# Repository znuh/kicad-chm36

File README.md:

# kicad-chm36
Interactive Web Browser based KiCad PCB to CHM-T36VA Pick&amp;Place File Converter  

This tool directly generates a CHM DPV file from a `.kicad_pcb` file (without exporting a `.pos` file in KiCad before).

**Conversion is done entirely in the browser. No PCB or Pick&amp;Place data is sent to a server.**  
Also, the tool only uses locally hosted (i.e. no external CDNs) [Bootstrap5](https://getbootstrap.com/) and vanilla Javascript **without** jQuery, Node.js, etc.

You can try it here: [https://znu.nz/kicad-chm36/](https://znu.nz/kicad-chm36/)

## Current Limitations
* PCB height cannot be set (yet)
* Single PCB mode only (no batch/array mode yet)
* Centroid correction not supported yet
* PCBs should be KiCad Version 8.0 or 7.0 (other versions might or might not work)

## Screenshot

## Basic Installation Instructions
* make the contents of the `web/` directory available via a HTTPS server
* use a browser to access the resource
* Chromium/Chrome instead of Firefox is recommended because Firefox does not (yet) implement the [window.showSaveFilePicker](https://developer.mozilla.org/en-US/docs/Web/API/Window/showSaveFilePicker#browser_compatibility) method. (Firefox will still work, but it'll just download the generated pick&amp;place file instead of showing a Save File Dialog.)

## Using the accompanying Golang Webserver in `server/`
**Note:** This webserver is optional. You can use any HTTPS webserver. This server offers an additional feature (see below) - if you don't need it you can use any HTTPS server. (You can then skip this section.)  
**Note:** While the server per se should work on Windows as well, instructions below are for UNIX-like Operating Systems (e.g. Linux, OSX, \*BSD).

`server/` contains a small HTTPS server written in Golang. Apart from serving the `web/` directory via HTTPS, this server can also serve all KiCad PCBs from a user-specified directory and all subdirectories. This can improve your workflow if the PCB files are located on a different computer than the PnP machine is connected to. You can also reload PCB files after they changed.  
It looks like this on the client side:  
  
To use the server you need to do the following:
* Install a working Golang environment and OpenSSL (for HTTPS cert/key generation)
* run `cd server/ && go build;cd ..`
* there should be a binary called `kicad-server` in the `server/` directory now
* you can now run the `./run_server.sh` script to test the server  
It will generate a key+certificate and start the server offering the test PCB from the `examples/` directory.

After this works you should modify the `./run_server.sh` script to fit your needs:
* Clients must be whitelisted with the `-allowed-ips=` option. You can specify single IPs and/or IP ranges.
* KiCad PCBs from the directory given with `-serve-pcbs=` (including all subdirectories) will be served. Only files with a `.kicad_pcb` suffix will be served.
* No PCBs will be served if the `-serve-pcbs=` option isn't given.

**Note:** The DPV reference file must be located on the client. The server does not offer a DPV reference file to the client.

## Matching PCB Components to Pick&amp;Place Feeders
The CHM DPV (CSV) file format doesn't have dedicated fields for listing the params of the components held by the feeders. There is only a `Note` field which can be used to store component information for a feeder. Instead of using an extra file to hold the component params for the feeders, this tool expects all relevant component params in the `Note` field of the feeder definitions.  
When entering the `Note` for a feeder, the CharmHigh software restricts the number of characters and blocks several characters. This can be overcome by using a text editor to edit the `Note` field. (Any simple editor such as Notepad is fine.) A long `Note` field is usually fine for the CHM software when loading a DPV file - even long Notes are usually displayed just fine. The length limit is only imposed during user input.  
When modifying the `Note` field with an editor you can also use nearly all characters such as spaces, dots and (semi)colons. **You must not use commas and line breaks though** because DPV files are CSV files with a comma separator. You cannot escape commas and quoting text also does not help. So just don't put a comma (or a line break) into the `Note` field.

This tool employs a reasonably intelligent approach for matching KiCad components to Pick&amp;Place feeders. A match occurs when the following conditions are satisfied:
* The KiCad **footprint** identifier (e.g. `C_0402_1005Metric`) must be found somewhere in the **Feeder Note**.
* After this the **KiCad Value** and the **Feeder Note** are treated as lists of whitespace separated params. (i.e. you put at least one space between different params - e.g.: `1uF 10V X5R`)
* The **first value** in this list is called the *Primary Value*. The *Primary Value* from KiCad and a feeder must be equal.  
  * **Units** are optional - e.g. a `10k` KiCad Primary Value will match a `10k` and a `10kR` feeder note.  
(Units are optional because the KiCad footprint identifier already includes the component type C/R/etc.)
  * However, if both the KiCad primary value and the Feeder Note primary value have a unit then these units must match.
  * Units `R` and `Ω` are treated as equivalent. (e.g. `10kR` and `10kΩ` will match)
  * Value comparison honors **multipliers** such as `p/n/u/µ/m/k/M/G` - i.e. `0.1uF` matches `0.1µF` and `100nF`; `10000` and `10k` also match.
  * **Limitation:** `1k5` will **not** match `1.5k`. Just avoid using the multiplier as the decimal point.
* While the KiCad and Feeder Primary Values must be equal for a match, there are also *Secondary Values* such as **ratings and tolerances**. For these values the Feeder Value must be **same or better** than the KiCad Value for a match.
  * Secondary Values are recognized by their unit (ratings: `V/A/W`, tolerances: `%/ppm`). If they are not recognized as rating or tolerance they must match exactly.
  * All KiCad Secondary Values must be satisfied by a Secondary Value from the Feeder Note.  
(Secondary Values only found in the Feeder Note but not in the KiCad Value are ignored - i.e. they don't inhibit a match.)
  * For **ratings** the feeder value must be equal or greater than the KiCad value
  * For **tolerances** the feeder value must be equal or less than the KiCad value
  * **Limitation 1:** Fractional notation (e.g. `1/8W`) isn't supported. Use notation with a decimal point (e.g. `0.125W`) instead.
  * **Limitation 2:** Temperature Coefficients such as **X7R** aren't recognized. This means that they must match exactly. A feeder with *X7R* in the note will not match a KiCad Value containing *X5R*. (If you don't add *X5R* to the KiCad value it can match the feeder if the other values are ok.)

The DPV and KiCad PCB files from the [examples](https://github.com/znuh/kicad-chm36/tree/main/examples) directory are selected to demonstrate several of the matching rules explained here.

### Feeder Note Example: ###
`0.1uF 25V X5R 10% fp:C_0402_1005Metric pn:CL05A104KA5NNNC`  
Note 1: I usually add the exact part number marked with `pn:` at the end of the Feeder Note. This does not break component matching.  
Note 2: I also prefer to prefix the footprint with `fp:` in the Feeder Note. This is also ok because for a match to occur the KiCad footprint identifier (`C_0402_1005Metric`) only needs to be found *somewhere* in the Feeder Note.

## Additional Named Feeder Params
The CHM DPV file format doesn't store the nozzle to use for a feeder in the Feeder Definition but in the individual component placement instruction (`PHead` as in PickHead in the `EComponent` lines). The DPV file also does not store the rotation of components in a certain feeder. Instead there's only the relative rotation of a component to apply during placement of a component. (`Angle` in the `EComponent` lines.)  
**Named Params** in the `Notes` field of a Feeder can be given to specify the **rotation** of components held in this feeder and to choose the **nozzle** to use for the Feeder:
* `nozzle:1` sets the nozzle to 1 (left nozzle). Nozzle 2 is the right nozzle. **Nozzle 1** will be used as the **default** when no **nozzle** param is given. (So you can just omit `nozzle:1` for nozzle 1.)
* `orientation:<angle>` can be used to specify the component rotation in a feeder relative to the KiCad 0° orientation. For reel feeders (Feeder IDs below 60) this is usually +90° (resulting in a -90° rotation to apply for a KiCad component with 0° orientation.)  
Specify the orientation without the degree sign - e.g. `orientation:90` / `orientation:-90`.  
When no component orientation is given for a feeder, a default orientation is selected based on the **Feeder ID**:
  * The default for IDs **below 60** (reel feeders) is a component orientation of +90°
  * The default for ID **60 and above** (IC trays and vibration feeders) is 0°  
* You can omit the `orientation:` param when the default orientation is correct.

## Preparing a DPV Reference File
Any existing DPV file can be used as a reference file - usually only minor modifications to the Feeder Notes are necessary. (See last two sections and the [example reference file](https://github.com/znuh/kicad-chm36/blob/main/examples/reference_example.dpv).)  
You can also create a new DPV file with the CharmHigh software if you do not have a DPV file yet.
Ensure that at least one `EComponent` line can be found in the DPV reference file. (It will be used as a template.)

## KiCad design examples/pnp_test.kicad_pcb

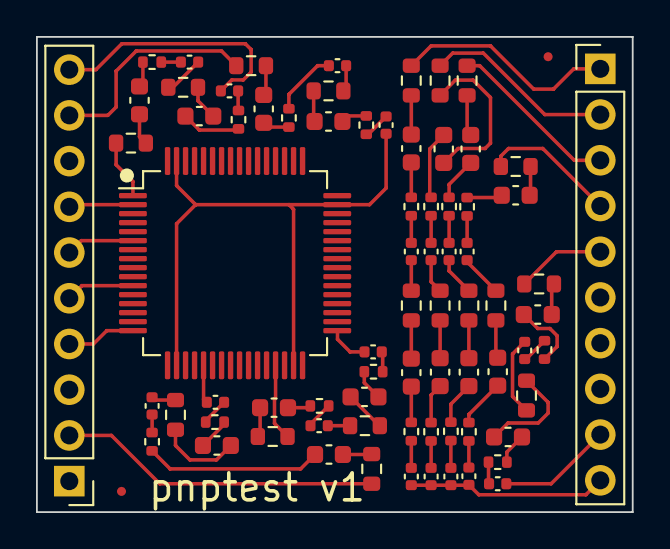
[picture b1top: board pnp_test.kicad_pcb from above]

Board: 2 copper layers, 33.1 x 26.4 mm, 77 parts (0 on the bottom side), 80 nets.

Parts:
C1, C3, C7, C17, C23, C31: 0.1uF; C_0402_1005Metric
C2, C6, C10, C12, C14, C16, C18, C20, C22, C24, C26, C30, C32, C34, C36: 0.1uF; C_0603_1608Metric
C4: 0.1u; C_0603_1608Metric
C5: 100nF; C_0402_1005Metric
C8: 0.1uF X7R 57V; C_0603_1608Metric
C9: 100nF 3V; C_0402_1005Metric
C11: 0.1µF 1V X5R; C_0402_1005Metric
C13: 0.1uF 5V; C_0402_1005Metric
C15: 100nF X5R; C_0402_1005Metric
C19: 0.1uF 11% 5V; C_0402_1005Metric
C21: 0.1uF 3nH; C_0402_1005Metric
C25: 100n; C_0402_1005Metric
C27: 0.1u; C_0402_1005Metric
C28: 0.10001uF; C_0603_1608Metric
C29: 0.1uF 2%; C_0402_1005Metric
C33: 0.1uF 20% 50V; C_0402_1005Metric
C35: 0.1µ; C_0402_1005Metric
FID1, FID2: Fiducial; Fiducial_0.5mm_Mask1.5mm
J1, J2: Conn_01x10_Pin; PinHeader_1x10_P2.54mm_Vertical
R1: 10k 0.0625W 1%; R_0402_1005Metric
R2, R4, R6, R8, R10, R12, R14, R16, R24, R26, R28, R30, R34, R36: 10k; R_0603_1608Metric
R3: 10k 1%; R_0402_1005Metric
R5, R7, R9, R13, R17, R19, R23, R25, R29, R33: 10k; R_0402_1005Metric
R11: 10k 0.06W; R_0402_1005Metric
R15: 10k 2W 1% 50kV; R_0402_1005Metric
R18: 10000R; R_0603_1608Metric
R20: 10kR; R_0603_1608Metric
R21: 10k 5% 10ppm; R_0402_1005Metric
R22: 10000; R_0603_1608Metric
R27: 10000Ω; R_0402_1005Metric
R31: 10k 49V; R_0402_1005Metric
R32: 10.001k; R_0603_1608Metric
R35: 10kΩ 50V; R_0402_1005Metric
U1: STM32F730R8Tx; LQFP-64_10x10mm_P0.5mm

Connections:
/1: R4.2, U1.1 (VBAT)
/2: J1.7, U1.2 (PC13)
/4: J1.4, U1.16 (PA2)
/5: J1.5, U1.11 (PC3)
/6: J1.6, U1.6 (PH1)
/21: C9.1, U1.21 (PA5)
/Ax1: J2.1, R28.2
/Ax2: J2.2, R32.2
/Ax3: J2.3, R36.2
/Ax4: J2.4, R16.2
/Ax5: J2.5, R20.2
/Ax9: C17.1, J2.9
/Ax10: C13.1, C25.1, C29.1, C33.1, J2.10
/Bx9: J1.9, R24.2
/Bx10: C1.1, J1.10
/x2: J1.2, R12.2
GND: C21.1, U1.18 (VSS), U1.31 (VSS), U1.47 (VSS), U1.63 (VSS)
unnamed: C1.2, R1.1
unnamed: C2.1, R1.2
unnamed: C2.2, R2.1
unnamed: C3.1, R2.2
unnamed: C3.2, R3.1
unnamed: C4.1, R3.2
unnamed: C4.2, R4.1
unnamed: C5.2, R5.1
unnamed: C6.1, R5.2
unnamed: C6.2, R6.1
unnamed: C7.1, R6.2
unnamed: C7.2, R7.1
unnamed: C8.1, R7.2
unnamed: C8.2, R8.1
unnamed: C9.2, R9.1
unnamed: C10.1, R9.2
unnamed: C10.2, R10.1
unnamed: C11.1, R10.2
unnamed: C11.2, R11.1
unnamed: C12.1, R11.2
unnamed: C12.2, R12.1
unnamed: C13.2, R13.1
unnamed: C14.1, R13.2
unnamed: C14.2, R14.1
unnamed: C15.1, R14.2
unnamed: C15.2, R15.1
unnamed: C16.1, R15.2
unnamed: C16.2, R16.1
unnamed: C17.2, R17.1
unnamed: C18.1, R17.2
unnamed: C18.2, R18.1
unnamed: C19.1, R18.2
unnamed: C19.2, R19.1
unnamed: C20.1, R19.2
unnamed: C20.2, R20.1
unnamed: C21.2, R21.1
unnamed: C22.1, R21.2
unnamed: C22.2, R22.1
unnamed: C23.1, R22.2
unnamed: C23.2, R23.1
unnamed: C24.1, R23.2
unnamed: C24.2, R24.1
unnamed: C25.2, R25.1
unnamed: C26.1, R25.2
unnamed: C26.2, R26.1
unnamed: C27.1, R26.2
unnamed: C27.2, R27.1
unnamed: C28.1, R27.2
unnamed: C28.2, R28.1
unnamed: C29.2, R29.1
unnamed: C30.1, R29.2
unnamed: C30.2, R30.1
unnamed: C31.1, R30.2
unnamed: C31.2, R31.1
unnamed: C32.1, R31.2
unnamed: C32.2, R32.1
unnamed: C33.2, R33.1
unnamed: C34.1, R33.2
unnamed: C34.2, R34.1
unnamed: C35.1, R34.2
unnamed: C35.2, R35.1
unnamed: C36.1, R35.2
unnamed: C36.2, R36.1

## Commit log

2023-05-14 initial import
2023-05-14 fix regex for PCB files from server: allow zero-length path
2023-05-14 clarify save as dialog stuff
2023-05-14 Update README.md
    add screenshot
2023-05-15 add some tooltips
2023-05-15 add version information, link to github and link to README
2023-05-15 add release notes
2023-05-15 HTML fixes
2023-05-15 update LICENSE
2023-05-15 clarify license stuff
2023-05-16 working on tooltips
2023-05-16 nozzle tooltip
2023-05-16 tooltips done
2023-05-22 remove unused extra components definition file
2023-05-22 add KiCad version check
2023-05-22 show KiCad version info either in green (ok) or yellow (warning)
2023-05-23 fix file write
2023-05-23 Update README.md - fix screenshot
2023-05-23 Update README.md - fix second screenshot
2023-06-13 fix release notes autohide
2023-06-13 make fiducial detection more robust
2023-06-13 treat '0.1uF/10V' like '0.1uF 10V' (accept first '/' as split symbol)
2023-06-17 fix feeder matching for non-number part identifiers (ICs, etc.)
2023-08-05 work on adding PCB offset
2023-08-05 add x/y offset for PCB
2024-02-24 add KiCad 8 support
2025-03-23 allow reupload of same file with new content
2025-03-23 allow uploading the same DPV-file with changed content as well
